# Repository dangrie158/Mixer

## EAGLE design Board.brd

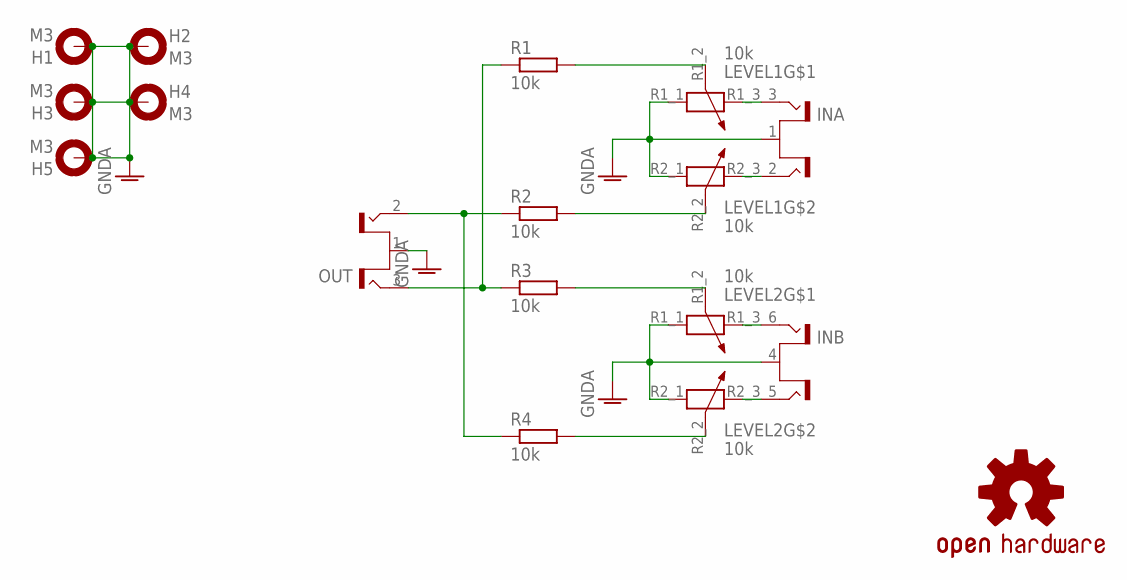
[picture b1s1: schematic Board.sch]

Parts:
H1, H2, H3, H4, H5: M3; 3,0-PAD
IN: RCA-4-117-01
LEVEL1, LEVEL2: 10k; ALPS-RK09L12B0
LOGO1: OSHW-LOGOL-COPPER; OSHW-LOGO-L_COPPER
OUT: RCA-2-117-01
R1, R2, R3, R4: 10k; 0414/15

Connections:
GNDA: H1.B3,0, H2.B3,0, H3.B3,0, H4.B3,0, H5.B3,0, IN.1 (S), IN.4 (S), LEVEL1.R1_1 (1), LEVEL1.R2_1 (1), LEVEL2.R1_1 (1), LEVEL2.R2_1 (1), OUT.1 (S)
unnamed: IN.6 (T2), LEVEL2.R1_3 (2)
unnamed: IN.3 (T2), LEVEL1.R1_3 (2)
unnamed: IN.2 (T1), LEVEL1.R2_3 (2)
unnamed: LEVEL1.R1_2 (3), R1.2
unnamed: LEVEL1.R2_2 (3), R2.2
unnamed: IN.5 (T1), LEVEL2.R2_3 (2)
unnamed: LEVEL2.R2_2 (3), R4.2
unnamed: LEVEL2.R1_2 (3), R3.2
unnamed: OUT.2 (T1), R2.1, R4.1
unnamed: OUT.3 (T2), R1.1, R3.1

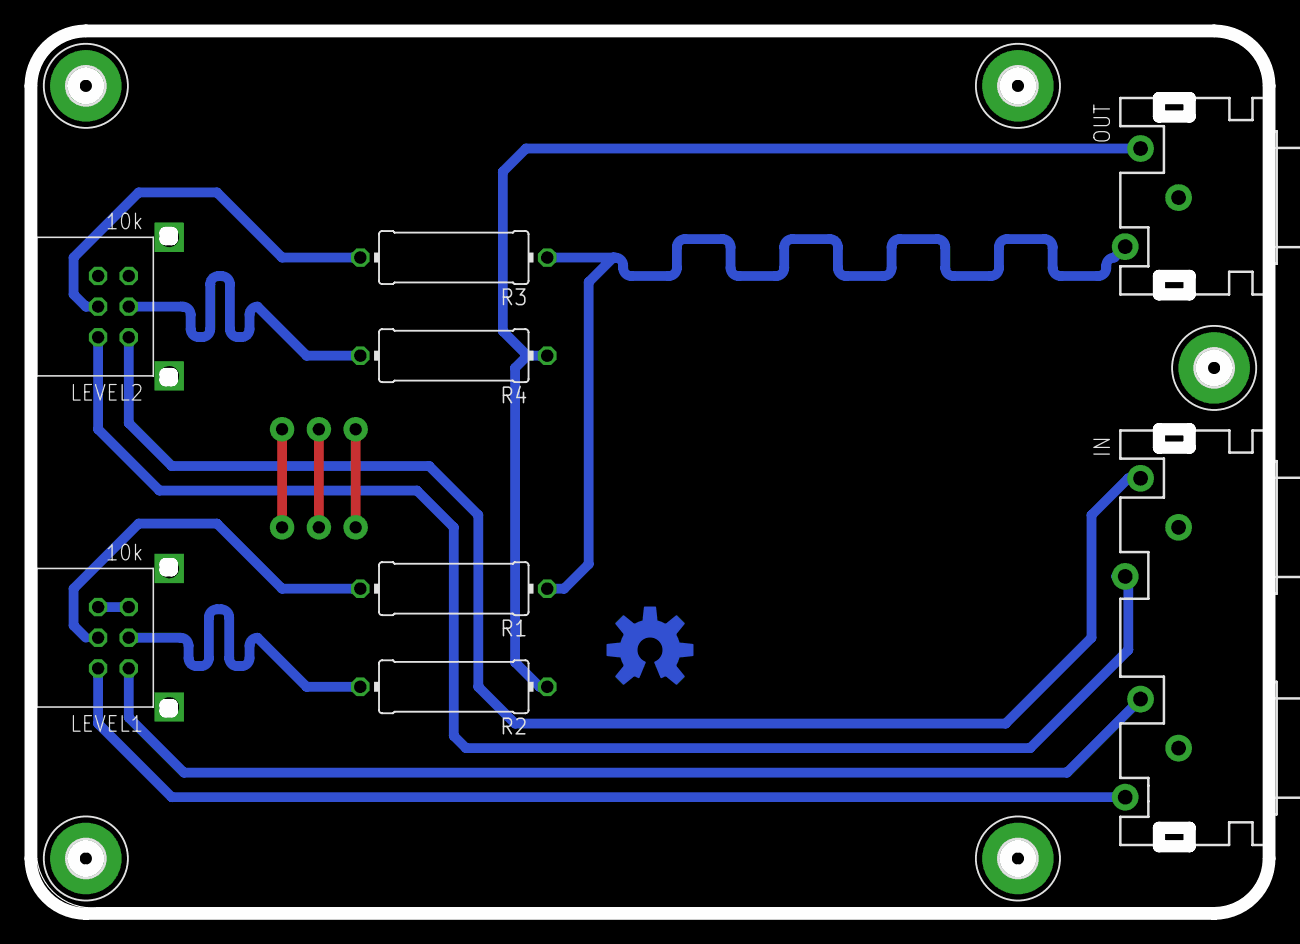
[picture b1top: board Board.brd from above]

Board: 2 copper layers, 101.0 x 72.0 mm, 14 parts (1 on the bottom side), 11 nets.

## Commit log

2018-12-11 updated Board and G-Code files

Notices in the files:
parts and their libraries:
SparkFun-Aesthetics: Licensing: Creative Commons ShareAlike 4.0 International - https://creativecommons.org/licenses/by-sa/4.0
